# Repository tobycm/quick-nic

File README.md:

# Quick NIC

A homemade USB 3 to Gigabit Ethernet adapter. Equipped with RTL8153B and MagJack connector (integrated magnetics) for small footprint.

## PCB

## BOM

| Description | Quantity | Part # | Unit price | Extended Price USD | Product Link |
|---|---|---|---|---|---|
| Crystal 25MHz ±10ppm 20pF 50Ω SMD3225-4P | 5 | XC32M4-25.000-F20NJDT | 0.07 | 0.37 | https://www.lcsc.com/product-detail/C2842189.html |
| QFN-40-EP(5x5) Drivers, Receivers, Transceivers | 1 | RTL8153B-VB-CG | 3.56 | 3.56 | https://www.lcsc.com/product-detail/C2802072.html |
| 33pF ±5% 50V Ceramic Capacitor C0G 0603 | 100 | CL10C330JB8NNNC | 0.01 | 0.64 | https://www.lcsc.com/product-detail/C1663.html |
| 10uF ±20% 25V Ceramic Capacitor X5R 0603 | 20 | CL10A106MA8NRNC | 0.08 | 1.55 | https://www.lcsc.com/product-detail/C96446.html |
| 1 Active Low 2.7A Load Switch SOT-23-6 Power Distribution Switches, Load Drivers | 5 | CH217A | 0.10 | 0.50 | https://www.lcsc.com/product-detail/C54973763.html |
| 220Ω@100MHz 1 Line Ferrite Bead 0805 2A 45mΩ | 20 | BLM21PG221SN1D | 0.03 | 0.69 | https://www.lcsc.com/product-detail/C85840.html |
| 1uF ±10% 50V Ceramic Capacitor X5R 0603 | 50 | CL10A105KB8NNNC | 0.02 | 0.83 | https://www.lcsc.com/product-detail/C15849.html |
| 2.49kΩ ±1% 100mW 0603 Thick Film Resistor | 100 | FRC0603F2491TS | 0.00 | 0.20 | https://www.lcsc.com/product-detail/C2930072.html |
| USB-A (USB TYPE-A) Receptacle Connector 9 Position Recessed Mount | 10 | HC-USB3.0-C26 | 0.11 | 1.11 | https://www.lcsc.com/product-detail/C7501854.html |
| 1nF ±10% 2kV Ceramic Capacitor X7R 1206 | 30 | 1206B102K202NT | 0.02 | 0.74 | https://www.lcsc.com/product-detail/C9196.html |
| 1MΩ ±5% 100mW 0603 Thick Film Resistor | 100 | FRC0603J105 TS | 0.00 | 0.17 | https://www.lcsc.com/product-detail/C2907115.html |
| 470Ω ±1% 100mW 0603 Thick Film Resistor | 100 | FRC0603F4700TS | 0.00 | 0.20 | https://www.lcsc.com/product-detail/C2907041.html |
| Jack Modular Connector RJ45 Through Hole | 5 | HR911130A | 2.51 | 12.54 | https://www.lcsc.com/product-detail/C54408.html |
| 62kΩ ±1% 100mW 0603 Thick Film Resistor | 100 | FRC0603F6202TS | 0.00 | 0.21 | https://www.lcsc.com/product-detail/C2907059.html |
| LCSC Shipping | | LCSC Shipping | 13.34 | 13.34 | https://www.lcsc.com/ |
| PCB | | PCB | 2.10 | 2.10 | https://jlcpcb.com/ |
| Stencil | | Stencil | 3.10 | 3.10 | https://jlcpcb.com/ |
| JLCPCB Shipping | | JLCPCB Shipping | 8.66 | 8.66 | https://jlcpcb.com/ |
| | | Total: | | 50.53 | |

## End notes

Made with <3 by @tobycm

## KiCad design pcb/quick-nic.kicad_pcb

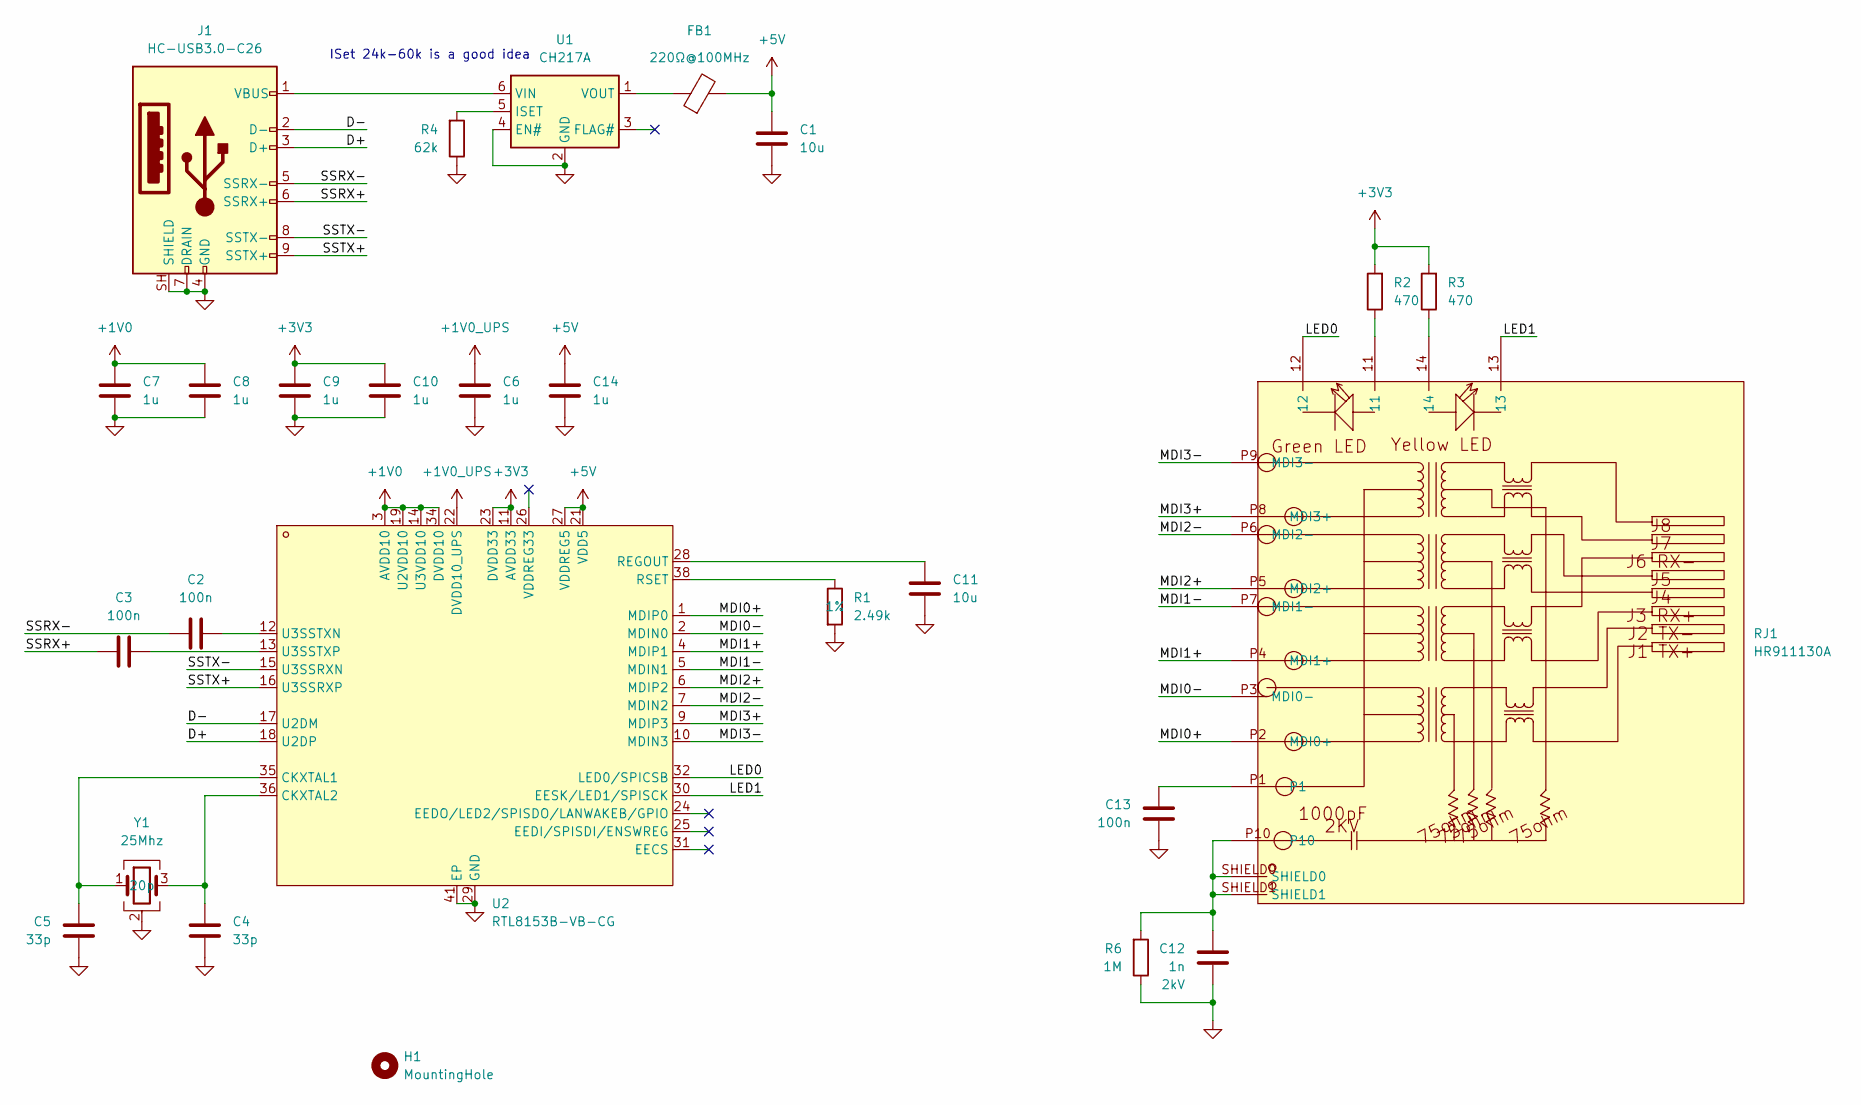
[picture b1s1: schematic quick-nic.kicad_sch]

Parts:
C1, C11: 10u; C_0603_1608Metric; LCSC Part C96446
C2, C3, C13: 100n; C_0603_1608Metric; LCSC Part C14663
C4, C5: 33p; C_0603_1608Metric; LCSC Part C1663
C6, C7, C8, C9, C10, C14: 1u; C_0603_1608Metric; LCSC Part C15849
C12: 1n; C_1206_3216Metric; Voltage Rating 2kV; LCSC Part C9196
FB1: 220Ω@100MHz; R_0805_2012Metric_Pad1.20x1.40mm_HandSolder; LCSC Part C85840
H1: MountingHole; MountingHole_3.2mm_M3_Pad
J1: HC-USB3.0-C26; USB-3.0-A-SMD_HC-USB3.0-C26
R1: 2.49k; R_0603_1608Metric; Tolerance 1%; LCSC Part C2930072
R2, R3: 470; R_0603_1608Metric; LCSC Part C2907041
R4: 62k; R_0603_1608Metric; LCSC Part C2907059
R6: 1M; R_0603_1608Metric; LCSC Part C2907115
RJ1: HR911130A; RJ45-TH_HR911130A; MPN HR911130A; LCSC Part C54408
U1: CH217A; SOT-23-6; LCSC Part C54973763
U2: RTL8153B-VB-CG; QFN-40-1EP_5x5mm_P0.4mm_EP3.6x3.6mm; MPN RTL8153B-VB-CG; LCSC Part C2802072
Y1: 25Mhz; Crystal_SMD_3225-4Pin_3.2x2.5mm

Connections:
+1V0: C7.1, C8.1, U2.3 (AVDD10), U2.8 (AVDD10), U2.14 (U3VDD10), U2.19 (U2VDD10), U2.34 (DVDD10), U2.37 (AVDD10)
+1V0_UPS: C6.1, U2.22 (DVDD10_UPS)
+3V3: C9.1, C10.1, R2.2, R3.2, U2.11 (AVDD33), U2.20 (AVDD33), U2.23 (DVDD33), U2.33 (DVDD33), U2.39 (AVDD33), U2.40 (AVDD33)
+5V: C1.2, C14.1, FB1.2, U2.21 (VDD5), U2.27 (VDDREG5)
/D+: J1.3 (D+), U2.18 (U2DP)
/D-: J1.2 (D-), U2.17 (U2DM)
/LED0: RJ1.12, U2.32 (LED0/SPICSB)
/LED1: RJ1.13, U2.30 (EESK/LED1/SPISCK)
/MDI0+: RJ1.P2 (MDI0+), U2.1 (MDIP0)
/MDI0-: RJ1.P3 (MDI0-), U2.2 (MDIN0)
/MDI1+: RJ1.P4 (MDI1+), U2.4 (MDIP1)
/MDI1-: RJ1.P7 (MDI1-), U2.5 (MDIN1)
/MDI2+: RJ1.P5 (MDI2+), U2.6 (MDIP2)
/MDI2-: RJ1.P6 (MDI2-), U2.7 (MDIN2)
/MDI3+: RJ1.P8 (MDI3+), U2.9 (MDIP3)
/MDI3-: RJ1.P9 (MDI3-), U2.10 (MDIN3)
/SSRX+: C3.2, J1.6 (SSRX+)
/SSRX-: C2.2, J1.5 (SSRX-)
/SSTX+: J1.9 (SSTX+), U2.16 (U3SSRXP)
/SSTX-: J1.8 (SSTX-), U2.15 (U3SSRXN)
GND: C1.1, C4.1, C5.1, C6.2, C7.2, C8.2, C9.2, C10.2, C11.1, C12.2, C13.2, C14.2, J1.4 (GND), J1.7 (DRAIN), J1.SH (SHIELD), R1.2, R4.1, R6.1, U1.2 (GND), U1.4 (EN#), U2.29 (GND), U2.41 (EP), Y1.2 (G), Y1.4 (G)
unnamed: C12.1, R6.2, RJ1.P10, RJ1.SHIELD0, RJ1.SHIELD1
unnamed: C13.1, RJ1.P1
unnamed: J1.1 (VBUS), U1.6 (VIN)
unnamed: R2.1, RJ1.11
unnamed: R3.1, RJ1.14
unnamed: R4.2, U1.5 (ISET)
unnamed: FB1.1, U1.1 (VOUT)
unnamed: C5.2, U2.35 (CKXTAL1), Y1.1
unnamed: C4.2, U2.36 (CKXTAL2), Y1.3
unnamed: C11.2, U2.28 (REGOUT)
unnamed: R1.1, U2.38 (RSET)
unnamed: C2.1, U2.12 (U3SSTXN)
unnamed: C3.1, U2.13 (U3SSTXP)

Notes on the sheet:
ISet 24k-60k is a good idea

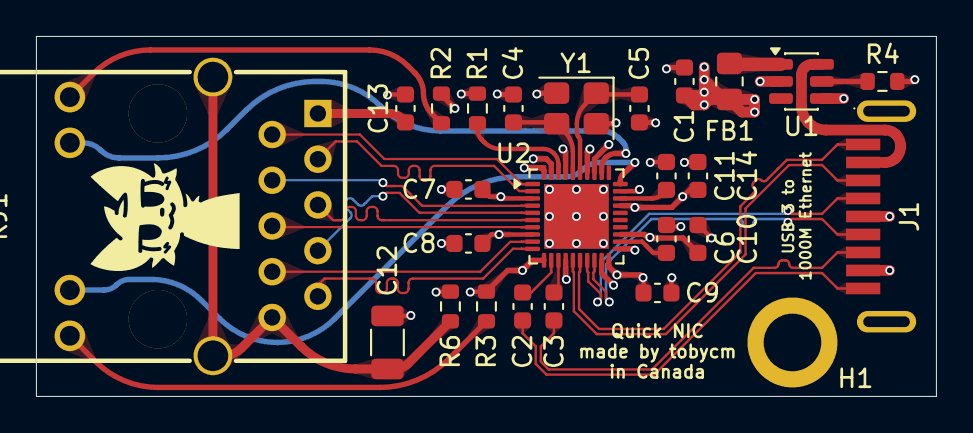
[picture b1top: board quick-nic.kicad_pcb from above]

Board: 6 copper layers, 50.0 x 20.0 mm, 26 parts (0 on the bottom side), 34 nets.

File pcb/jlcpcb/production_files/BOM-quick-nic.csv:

Comment,Designator,Footprint,LCSC,Quantity
100n,"C13,C2,C3",C_0603_1608Metric,C14663,3
10u,"C1,C11",C_0603_1608Metric,C96446,2
1M,R6,R_0603_1608Metric,C2907115,1
1n,C12,C_1206_3216Metric,C9196,1
1u,"C10,C14,C6,C7,C8,C9",C_0603_1608Metric,C15849,6
2.49k,R1,R_0603_1608Metric,C2930072,1
220Ω@100MHz,FB1,R_0805_2012Metric_Pad1.20x1.40mm_HandSolder,C85840,1
33p,"C4,C5",C_0603_1608Metric,C1663,2
470,"R2,R3",R_0603_1608Metric,C2907041,2
62k,R4,R_0603_1608Metric,C2907059,1
CH217A,U1,SOT-23-6,C54973763,1
HC-USB3.0-C26,J1,USB-3.0-A-SMD_HC-USB3.0-C26,C7501854,1
HR911130A,RJ1,RJ45-TH_HR911130A,C54408,1
RTL8153B-VB-CG,U2,QFN-40-1EP_5x5mm_P0.4mm_EP3.6x3.6mm,C2802072,1
25Mhz,Y1,Crystal_SMD_3225-4Pin_3.2x2.5mm,,1
